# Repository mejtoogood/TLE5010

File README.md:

# TLE5010 Magnetoresistive Angle Sensor 

Infineon TLE5010 GMR Sensor <a href="https://www.digchip.com/datasheets/download_datasheet.php?id=2688384&part-number=TLE5010">datasheet</a> - up to 16 bit angular resolution over SPI

Derived from TLE5010 PCB design by the <a href="github.com/mmjoy">MMJoy Project</a>

Order three PCBs for $10 shipped free worldwide using [OSH Park](https://oshpark.com) - simply upload the Eagle CAD .brd file from this repo to OSH Park and you’re set…

<br />This work is licensed under a <a rel="license" href="http://creativecommons.org/licenses/by-nc-sa/4.0/">Creative Commons Attribution-NonCommercial-ShareAlike 4.0 International License</a>.

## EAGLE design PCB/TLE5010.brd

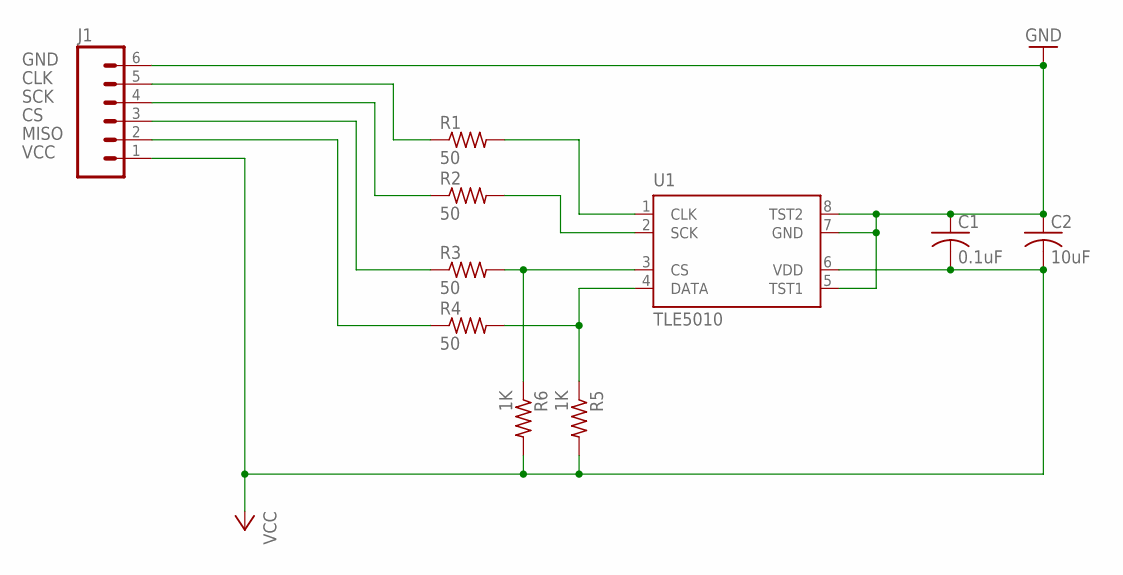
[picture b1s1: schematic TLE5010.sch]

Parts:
C1: 0.1uF; C1206
C2: 10uF; C1206
J1: M06POLAR_LOCK; MOLEX-1X6_LOCK
R1, R2, R3, R4: 50; R1206
R5, R6: 1K; R1206
U1: TLE5010; PG-DSO-8

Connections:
CLK: J1.5, R1.1
CS: J1.3, R3.1
DATA: R4.2, R5.1, U1.4 (DATA)
GND: C1.1, C2.1, J1.6, U1.5 (TST1), U1.7 (GND), U1.8 (TST2)
MISO: J1.2, R4.1
unnamed: R1.2, U1.1 (CLK)
unnamed: R2.2, U1.2 (SCK)
unnamed: R3.2, R6.1, U1.3 (CS)
SCK: J1.4, R2.1
VCC: C1.2, C2.2, J1.1, R5.2, R6.2, U1.6 (VDD)

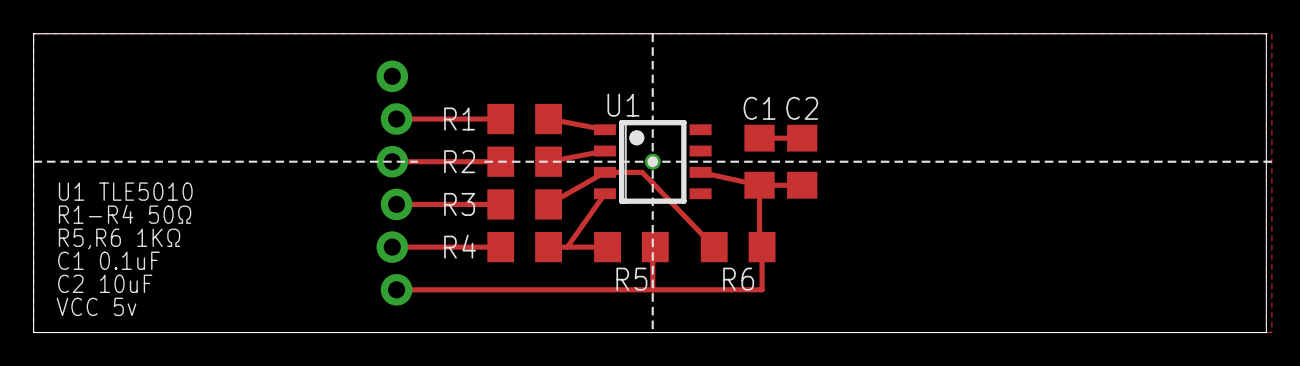
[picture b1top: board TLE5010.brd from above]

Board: 2 copper layers, 73.3 x 17.8 mm, 10 parts (1 on the bottom side), 10 nets.

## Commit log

2016-05-16 Directory structure
2016-05-16 Fixed R5, R6 copper pour
    Routing went weird when I moved R5 & R6 east, re-routed to improve
    ground plane copper pour
2016-05-17 Turned the middle side top-wise
2016-05-17 Fixed J1 orientation
    now corresponds with Cougar MMjoy board headers

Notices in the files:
parts and their libraries:
SparkFun-Connectors: Licensing: Creative Commons ShareAlike 4.0 International - https://creativecommons.org/licenses/by-sa/4.0
